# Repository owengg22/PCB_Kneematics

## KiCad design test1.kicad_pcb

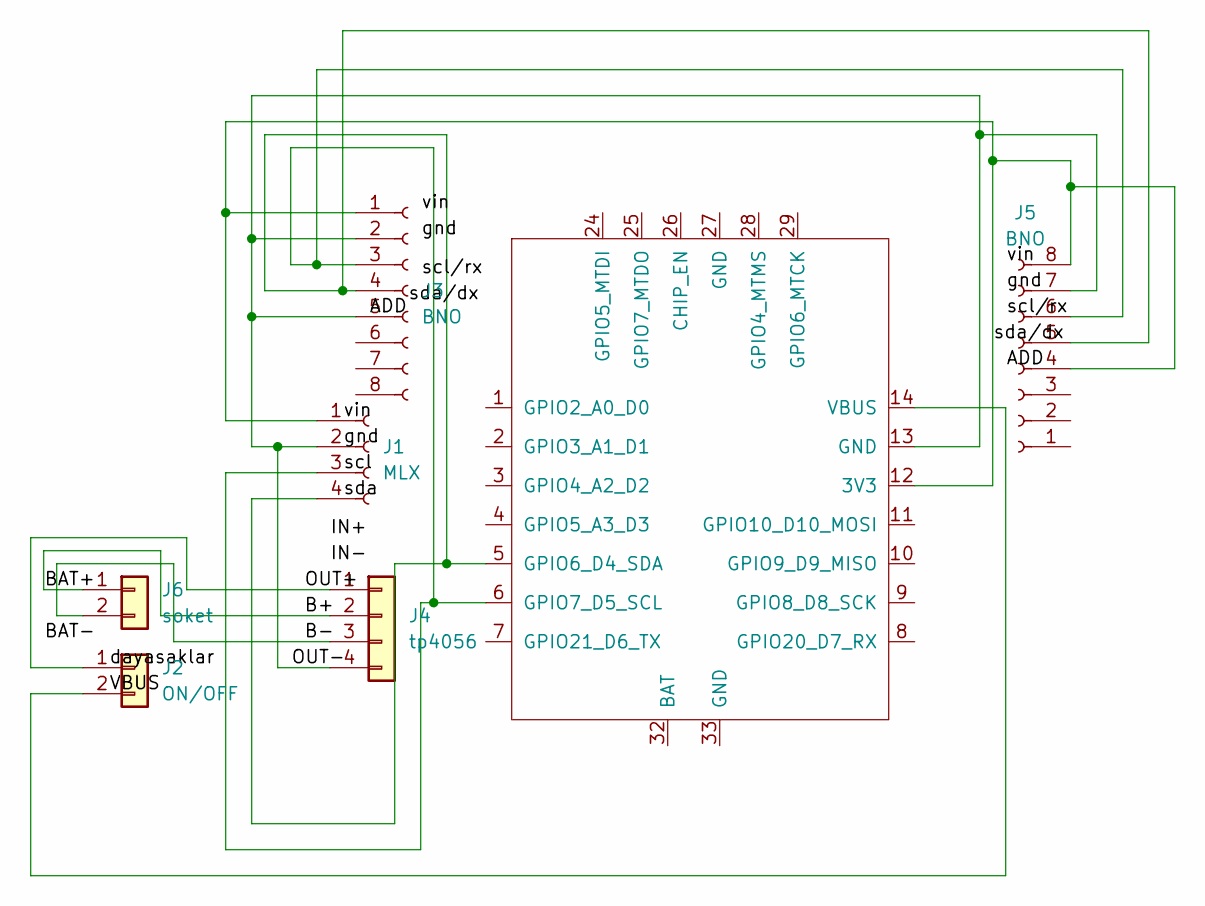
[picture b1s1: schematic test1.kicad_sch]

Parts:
J1: MLX; PinHeader_1x04_P2.54mm_Vertical
J2: ON/OFF; PinHeader_1x02_P2.54mm_Vertical
J3, J5: BNO; PinHeader_1x08_P2.54mm_Vertical
J4: tp4056; PinHeader_1x04_P2.54mm_Vertical
J6: soket; PinHeader_1x02_P2.54mm_Vertical
U1: XIAO-ESP32-C3-SMD

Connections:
/B+: J4.2, J6.1
/B-: J4.3, J6.2
/OUT+: J2.1, J4.1
/OUT-: J1.2, J3.2, J3.5, J4.4, J5.7, U1.13 (GND)
/sda/dx: J1.1, J3.1, J5.4, J5.8, U1.12 (3V3)
unnamed: J1.3, J3.3, J5.6, U1.6 (GPIO7_D5_SCL)
unnamed: J1.4, J3.4, J5.5, U1.5 (GPIO6_D4_SDA)
unnamed: J2.2, U1.14 (VBUS)

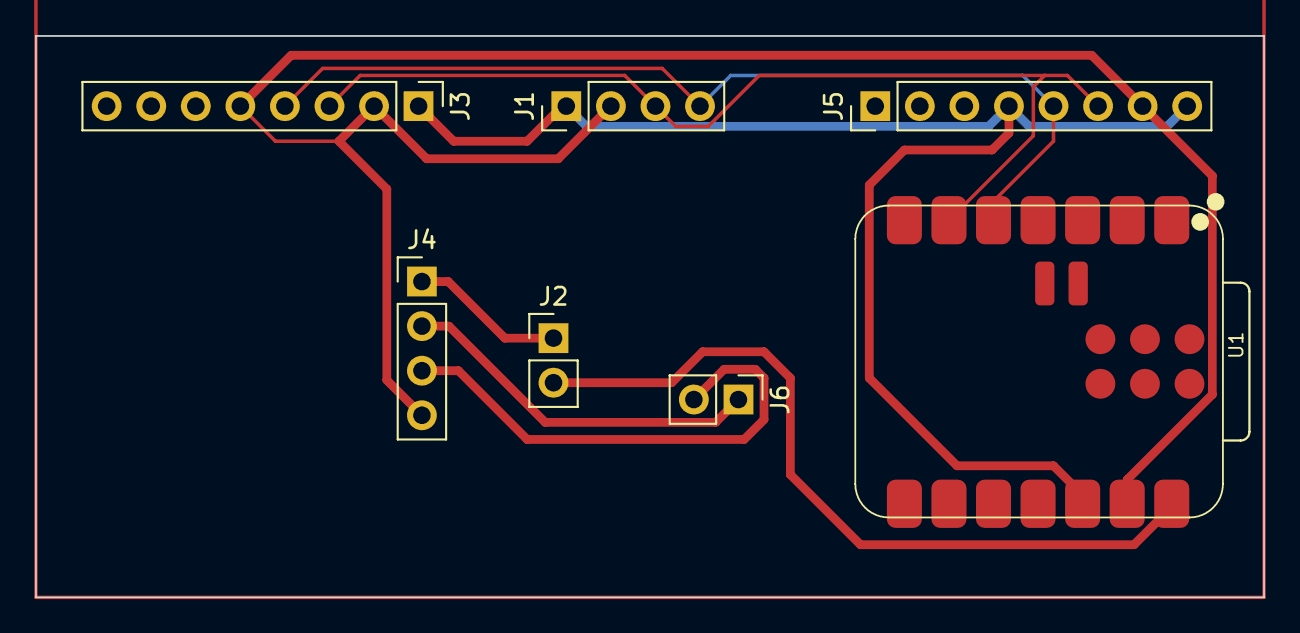
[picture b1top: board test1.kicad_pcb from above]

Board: 2 copper layers, 70.0 x 32.0 mm, 7 parts (0 on the bottom side), 8 nets.

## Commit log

2026-03-23 First commit purwarupa KNEEMATICS v1.0
2026-03-24 upd sedikit
2026-03-26 upd sedikitlagi - beresin footprint sama stl
